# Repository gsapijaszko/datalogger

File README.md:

# yet another datalogger
atmega, sdcard, usb port, DS3231 RTC

work in progress..

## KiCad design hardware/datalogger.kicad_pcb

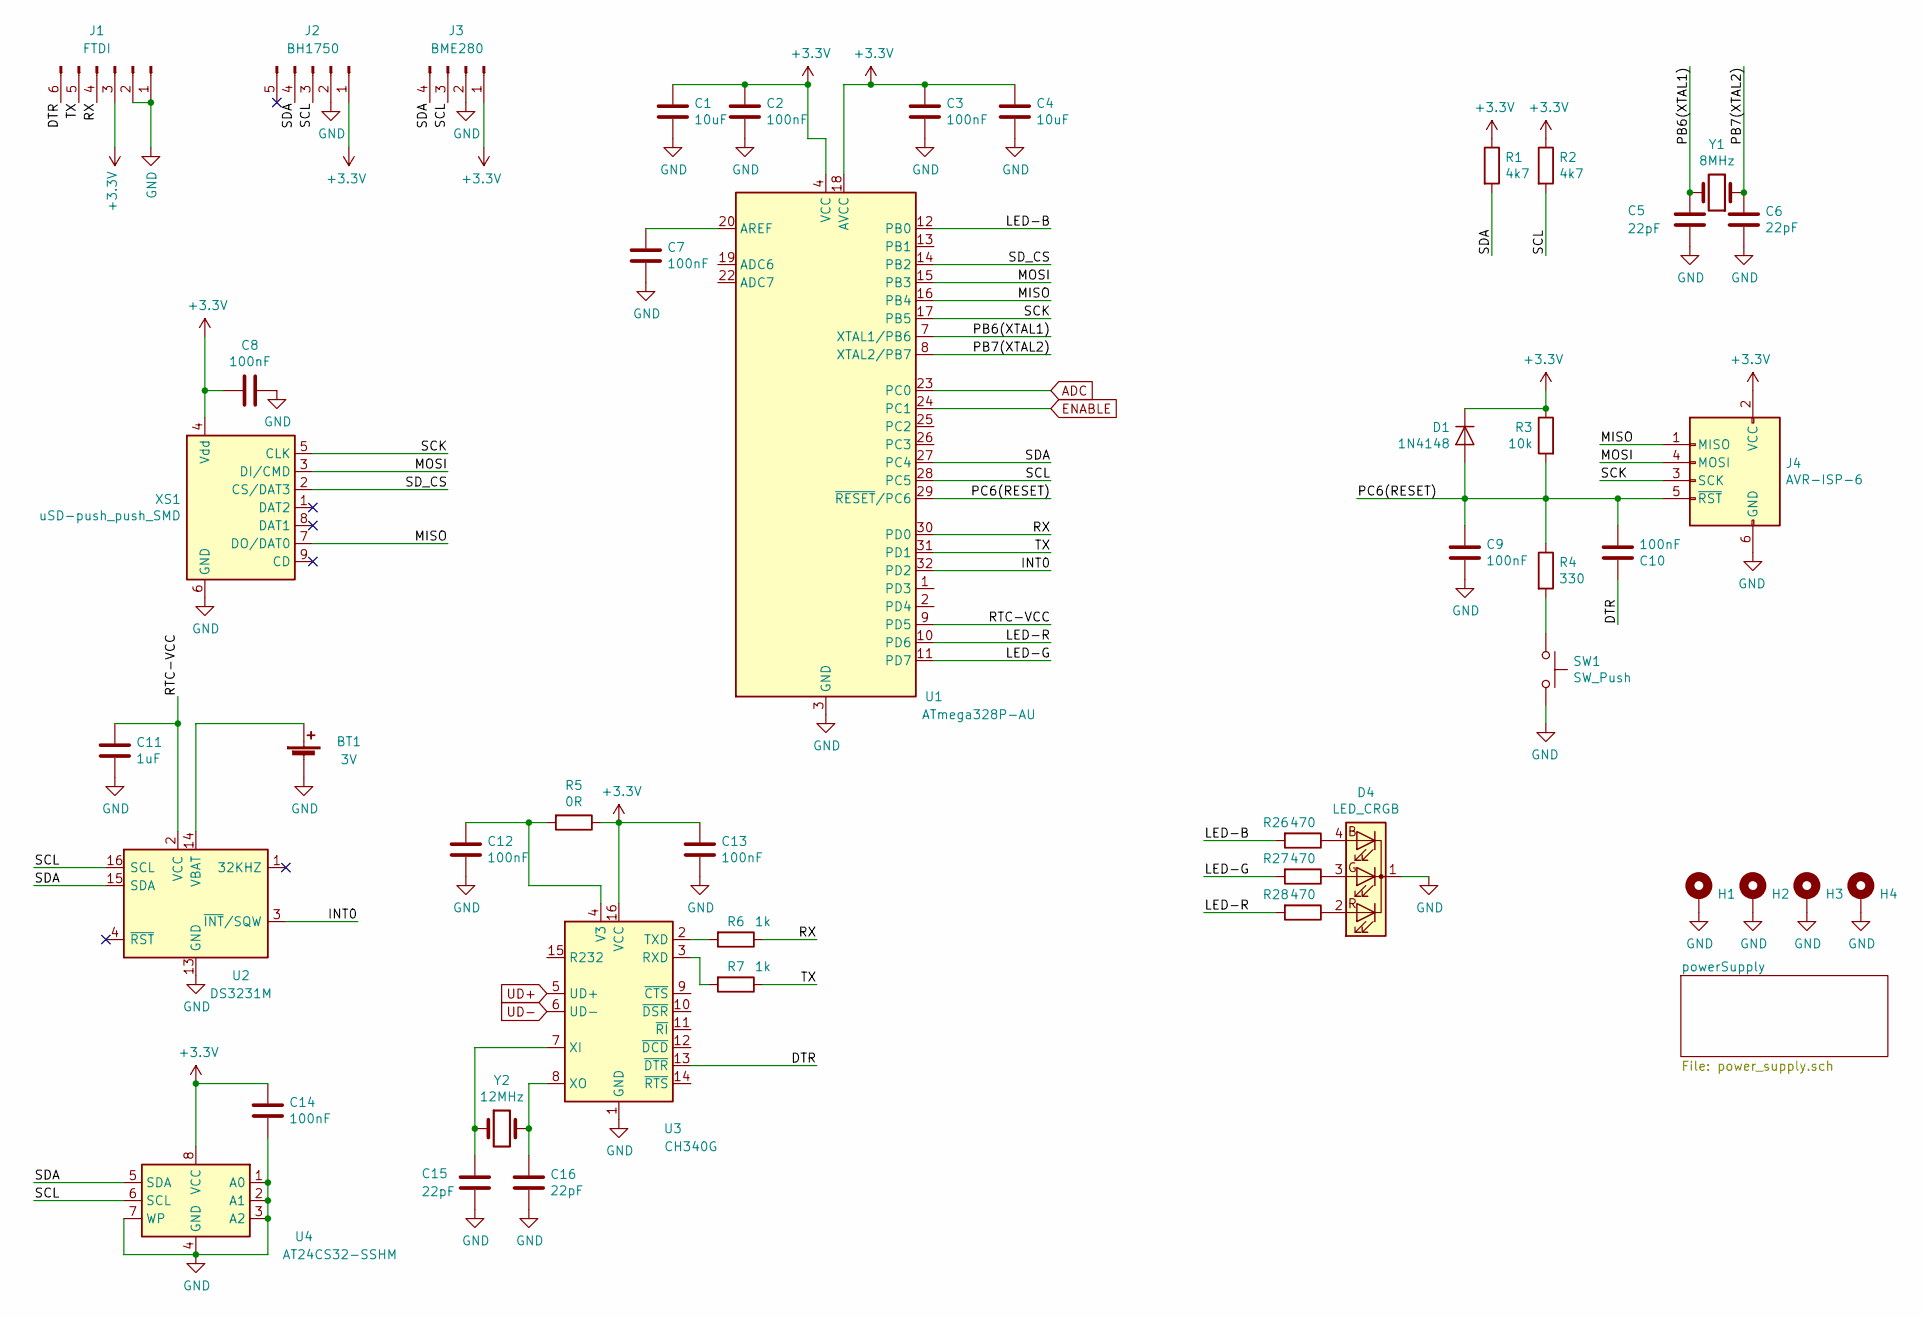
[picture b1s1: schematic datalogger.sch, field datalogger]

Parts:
BT1: 3V; 1220 Battery Holder, SMD
C1, C4: 10uF; C_0805_2012Metric_Pad1.15x1.40mm_HandSolder
C2, C3, C7, C8, C9, C12, C13, C14: 100nF; C_0805_2012Metric_Pad1.15x1.40mm_HandSolder
C5, C6, C15, C16: 22pF; C_1206_3216Metric_Pad1.42x1.75mm_HandSolder
C10: 100nF; C_1206_3216Metric_Pad1.42x1.75mm_HandSolder
C11: 1uF; C_0805_2012Metric_Pad1.15x1.40mm_HandSolder
D1: 1N4148; D_DO-34_SOD68_P7.62mm_Horizontal
D4: LED_CRGB; LED_D5.0mm-4_RCGB
H1, H2, H3, H4: H; MountingHole_2.7mm_M2.5_Pad_Via
J1: FTDI; PinHeader_1x06_P2.54mm_Vertical
J2: BH1750; Molex_KK-254_AE-6410-05A_1x05_P2.54mm_Vertical
J3: BME280; Molex_KK-254_AE-6410-04A_1x04_P2.54mm_Vertical
J4: AVR-ISP-6; IDC-Header_2x03_P2.54mm_Vertical
R1, R2: 4k7; R_0805_2012Metric_Pad1.15x1.40mm_HandSolder
R3: 10k; R_1206_3216Metric_Pad1.42x1.75mm_HandSolder
R4: 330; R_0805_2012Metric_Pad1.15x1.40mm_HandSolder
R5: 0R; R_0805_2012Metric_Pad1.15x1.40mm_HandSolder
R6, R7: 1k; R_0805_2012Metric_Pad1.15x1.40mm_HandSolder
R26, R27, R28: 470; R_1206_3216Metric_Pad1.42x1.75mm_HandSolder
SW1: SW_Push; SW_Tactile_SKHH_Angled
U1: ATmega328P-AU; TQFP-32_7x7mm_P0.8mm
U2: DS3231M; SOIC-16W_7.5x10.3mm_P1.27mm
U3: CH340G; SOIC-16_3.9x9.9mm_P1.27mm
U4: AT24CS32-SSHM; SOIC-8_3.9x4.9mm_P1.27mm
XS1: uSD-push_push_SMD; Conn_uSDcard
Y1: 8MHz; Crystal_HC49-U_Vertical
Y2: 12MHz; Crystal_HC49-U_Vertical

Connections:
+3V3: C1.1, C2.2, C3.2, C4.1, C8.1, C13.2, C14.1, D1.1 (K), J1.3, J2.1, J3.1, J4.2 (VCC), R1.1, R2.1, R3.1, R5.1, U1.4 (VCC), U1.6 (VCC), U1.18 (AVCC), U3.16 (VCC), U4.8 (VCC), XS1.4 (Vdd); also elsewhere on the board
/DTR: C10.1, J1.6, U3.13 (~DTR)
/INT0: U1.32 (PD2), U2.3 (~INT~/SQW)
/LED-B: R26.2, U1.12 (PB0)
/LED-G: R27.2, U1.11 (PD7)
/LED-R: R28.2, U1.10 (PD6)
/MISO: J4.1 (MISO), U1.16 (PB4), XS1.7 (DO/DAT0)
/MOSI: J4.4 (MOSI), U1.15 (PB3), XS1.3 (DI/CMD)
/PB6(XTAL1): C5.1, U1.7 (XTAL1/PB6), Y1.2
/PB7(XTAL2): C6.1, U1.8 (XTAL2/PB7), Y1.1
/PC6(RESET): C9.1, C10.2, D1.2 (A), J4.5 (~RST), R3.2, R4.1, U1.29 (~RESET~/PC6)
/RTC-VCC: C11.1, U1.9 (PD5), U2.2 (VCC)
/RX: J1.4, R6.1, U1.30 (PD0)
/SCK: J4.3 (SCK), U1.17 (PB5), XS1.5 (CLK)
/SCL: J2.3, J3.3, R2.2, U1.28 (PC5), U2.16 (SCL), U4.6 (SCL)
/SDA: J2.4, J3.4, R1.2, U1.27 (PC4), U2.15 (SDA), U4.5 (SDA)
/SD_CS: U1.14 (PB2), XS1.2 (CS/DAT3)
/TX: J1.5, R7.1, U1.31 (PD1)
ADC: U1.23 (PC0); also elsewhere on the board
ENABLE: U1.24 (PC1); also elsewhere on the board
GND: BT1.2 (-), C1.2, C2.1, C3.1, C4.2, C5.2, C6.2, C7.2, C8.2, C9.2, C11.2, C12.1, C13.1, C14.2, C15.2, C16.2, D4.1 (K), H1.1, H2.1, H3.1, H4.1, J1.1, J1.2, J2.2, J3.2, J4.6 (GND), SW1.2, U1.3 (GND), U1.5 (GND), U1.21 (GND), U2.5 (GND), U2.6 (GND), U2.7 (GND), U2.8 (GND), U2.9 (GND), U2.10 (GND), U2.11 (GND), U2.12 (GND), U2.13 (GND), U3.1 (GND), U4.1 (A0), U4.2 (A1), U4.3 (A2), U4.4 (GND), U4.7 (WP), XS1.6 (GND); also elsewhere on the board
unnamed: BT1.1 (+), U2.14 (VBAT)
unnamed: C7.1, U1.20 (AREF)
unnamed: C12.2, R5.2, U3.4 (V3)
unnamed: C15.1, U3.7 (XI), Y2.1
unnamed: C16.1, U3.8 (XO), Y2.2
unnamed: D4.2 (RA), R28.1
unnamed: D4.3 (GA), R27.1
unnamed: D4.4 (BA), R26.1
unnamed: R4.2, SW1.1
unnamed: R6.2, U3.2 (TXD)
unnamed: R7.2, U3.3 (RXD)
UD+: U3.5 (UD+); also elsewhere on the board
UD-: U3.6 (UD-); also elsewhere on the board

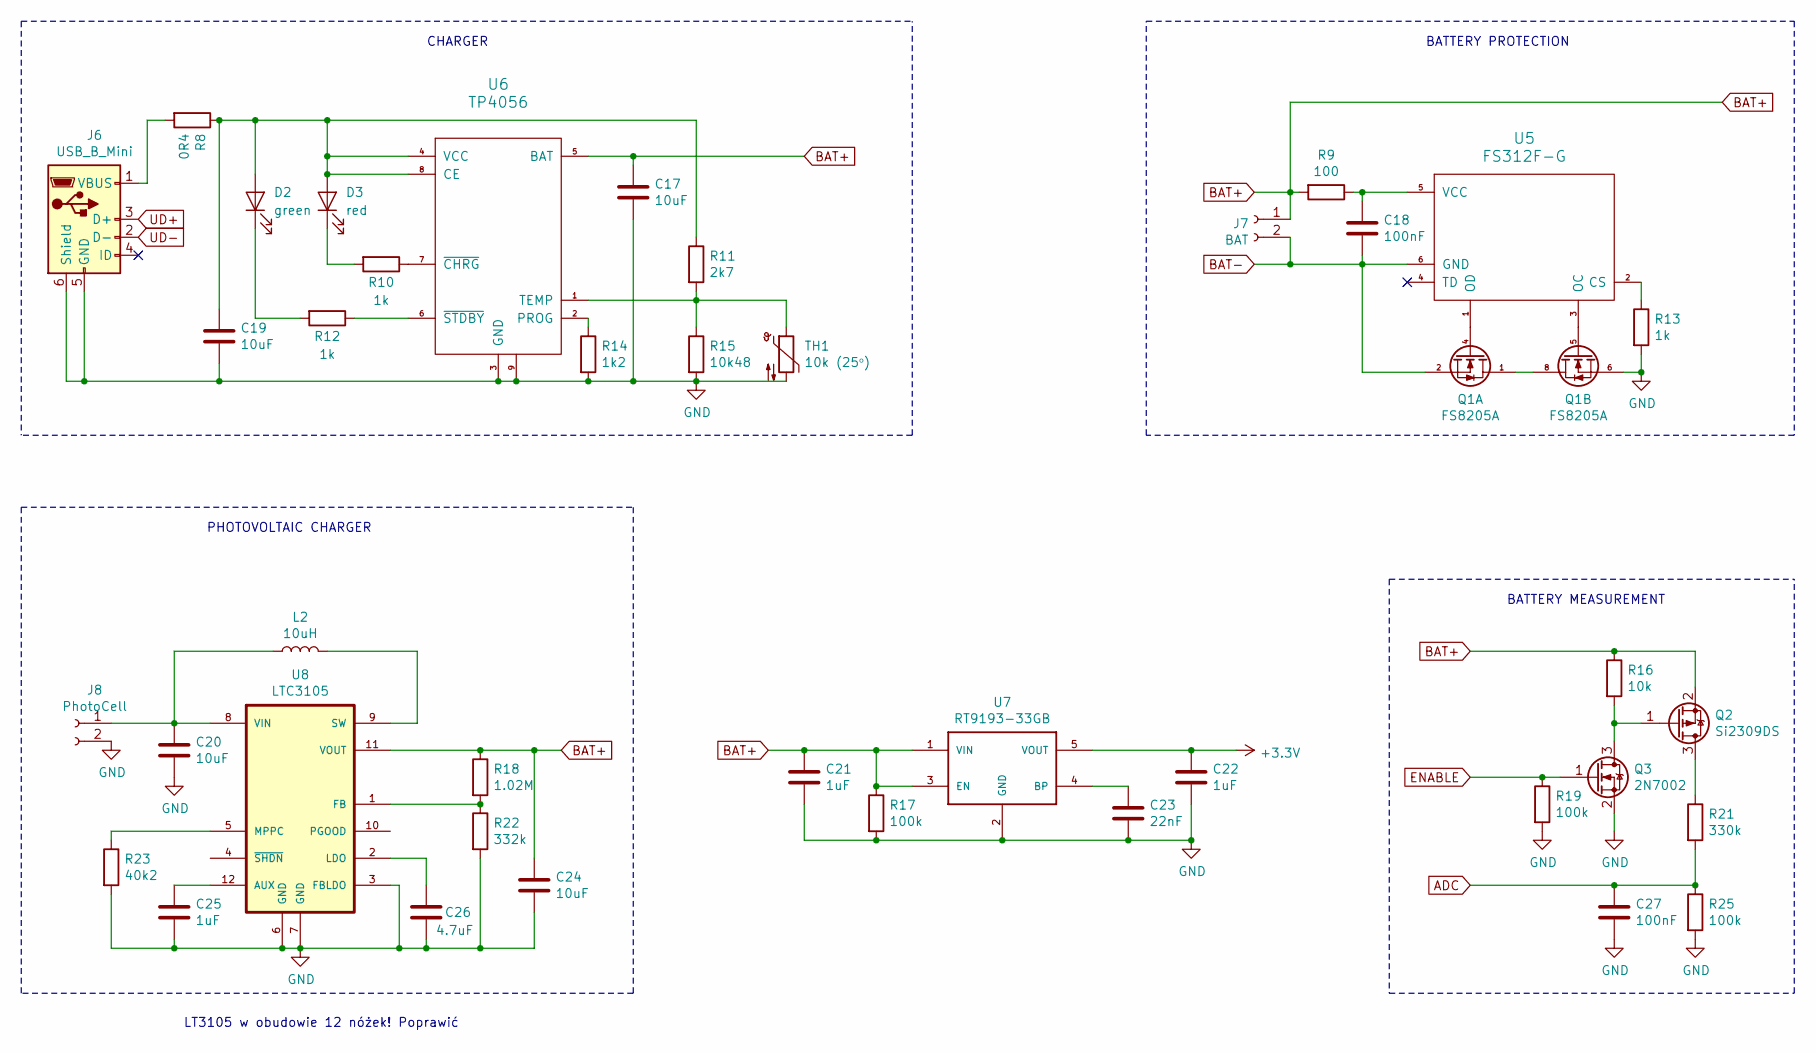
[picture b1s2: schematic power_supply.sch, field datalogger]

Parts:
C17, C19, C20, C24: 10uF; C_1206_3216Metric_Pad1.42x1.75mm_HandSolder
C18, C27: 100nF; C_0805_2012Metric_Pad1.15x1.40mm_HandSolder
C21, C22: 1uF; C_0805_2012Metric_Pad1.15x1.40mm_HandSolder
C23: 22nF; C_0805_2012Metric_Pad1.15x1.40mm_HandSolder
C25: 1uF; C_0805_2012Metric
C26: 4.7uF; C_0805_2012Metric
D2: green; LED_1210_3225Metric_Pad1.42x2.65mm_HandSolder
D3: red; LED_1210_3225Metric_Pad1.42x2.65mm_HandSolder
J6: USB_B_Mini; USB_Micro-B_Wuerth_629105150521
J7: BAT; JST_XH_S02B-XH-A_1x02_P2.50mm_Horizontal
J8: PhotoCell; TerminalBlock_Altech_AK300-2_P5.00mm
L2: 10uH; L_7.3x7.3_H4.5
Q1: FS8205A; TSSOP-8_4.4x3mm_P0.65mm
Q2: Si2309DS; SOT-23
Q3: 2N7002; TSOT-23
R8: 0R4; R_1210_3225Metric_Pad1.42x2.65mm_HandSolder
R9: 100; R_1206_3216Metric_Pad1.42x1.75mm_HandSolder
R10, R12, R13: 1k; R_0805_2012Metric_Pad1.15x1.40mm_HandSolder
R11: 2k7; R_1206_3216Metric_Pad1.42x1.75mm_HandSolder
R14: 1k2; R_1206_3216Metric_Pad1.42x1.75mm_HandSolder
R15: 10k48; R_0805_2012Metric_Pad1.15x1.40mm_HandSolder
R16: 10k; R_1206_3216Metric_Pad1.42x1.75mm_HandSolder
R17, R19, R25: 100k; R_1206_3216Metric_Pad1.42x1.75mm_HandSolder
R18: 1.02M; R_1206_3216Metric_Pad1.42x1.75mm_HandSolder
R21: 330k; R_1206_3216Metric_Pad1.42x1.75mm_HandSolder
R22: 332k; R_1206_3216Metric_Pad1.42x1.75mm_HandSolder
R23: 40k2; R_1206_3216Metric_Pad1.42x1.75mm_HandSolder
TH1: 10k (25ᵒ); R_1218_3246Metric_Pad1.22x4.75mm_HandSolder
U5: FS312F-G; SOT-23-6_Handsoldering
U6: TP4056; HSOP-8-1EP_3.9x4.9mm_P1.27mm_EP2.41x3.1mm_ThermalVias
U7: RT9193-33GB; SOT-23-5_HandSoldering
U8: LTC3105; MSOP-12_3x4mm_P0.65mm

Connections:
+3V3: C22.1, U7.5 (VOUT); also elsewhere on the board
ADC: C27.1, R21.2, R25.1; also elsewhere on the board
BAT+: C17.1, C21.1, C24.1, J7.1, Q2.2 (S), R9.2, R16.1, R17.1, R18.1, U6.5 (BAT), U7.1 (VIN), U7.3 (EN), U8.11 (VOUT)
BAT-: C18.2, J7.2, Q1.2 (S1), U5.6 (GND)
ENABLE: Q3.1 (G), R19.1; also elsewhere on the board
GND: C17.2, C19.2, C20.2, C21.2, C22.2, C23.2, C24.2, C25.2, C26.2, C27.2, J6.5 (GND), J6.6 (Shield), J8.2, Q1.6 (S1), Q3.2 (S), R13.2, R14.2, R15.2, R17.2, R19.2, R22.2, R23.2, R25.2, TH1.2, U6.3 (GND), U6.9, U7.2 (GND), U8.3 (FBLDO), U8.6 (GND), U8.7 (GND); also elsewhere on the board
unnamed: C18.1, R9.1, U5.5 (VCC)
unnamed: C19.1, D2.2 (A), D3.2 (A), R8.1, R11.1, U6.4 (VCC), U6.8 (CE)
unnamed: C20.1, J8.1, L2.1, U8.8 (VIN)
unnamed: C23.1, U7.4 (BP)
unnamed: C25.1, U8.12 (AUX)
unnamed: C26.1, U8.2 (LDO)
unnamed: D2.1 (K), R12.2
unnamed: D3.1 (K), R10.2
unnamed: J6.1 (VBUS), R8.2
unnamed: L2.2, U8.9 (SW)
unnamed: Q1.1 (D), Q1.8 (D)
unnamed: Q1.4 (G2), U5.1 (OD)
unnamed: Q1.5 (G2), U5.3 (OC)
unnamed: Q2.1 (G), Q3.3 (D), R16.2
unnamed: Q2.3 (D), R21.1
unnamed: R10.1, U6.7 (~CHRG)
unnamed: R11.2, R15.1, TH1.1, U6.1 (TEMP)
unnamed: R12.1, U6.6 (~STDBY)
unnamed: R13.1, U5.2 (CS)
unnamed: R14.1, U6.2 (PROG)
unnamed: R18.2, R22.1, U8.1 (FB)
unnamed: R23.1, U8.5 (MPPC)
UD+: J6.3 (D+); also elsewhere on the board
UD-: J6.2 (D-); also elsewhere on the board

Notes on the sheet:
CHARGER
BATTERY PROTECTION
BATTERY MEASUREMENT
PHOTOVOLTAIC CHARGER
LT3105 w obudowie 12 nóżek! Poprawić

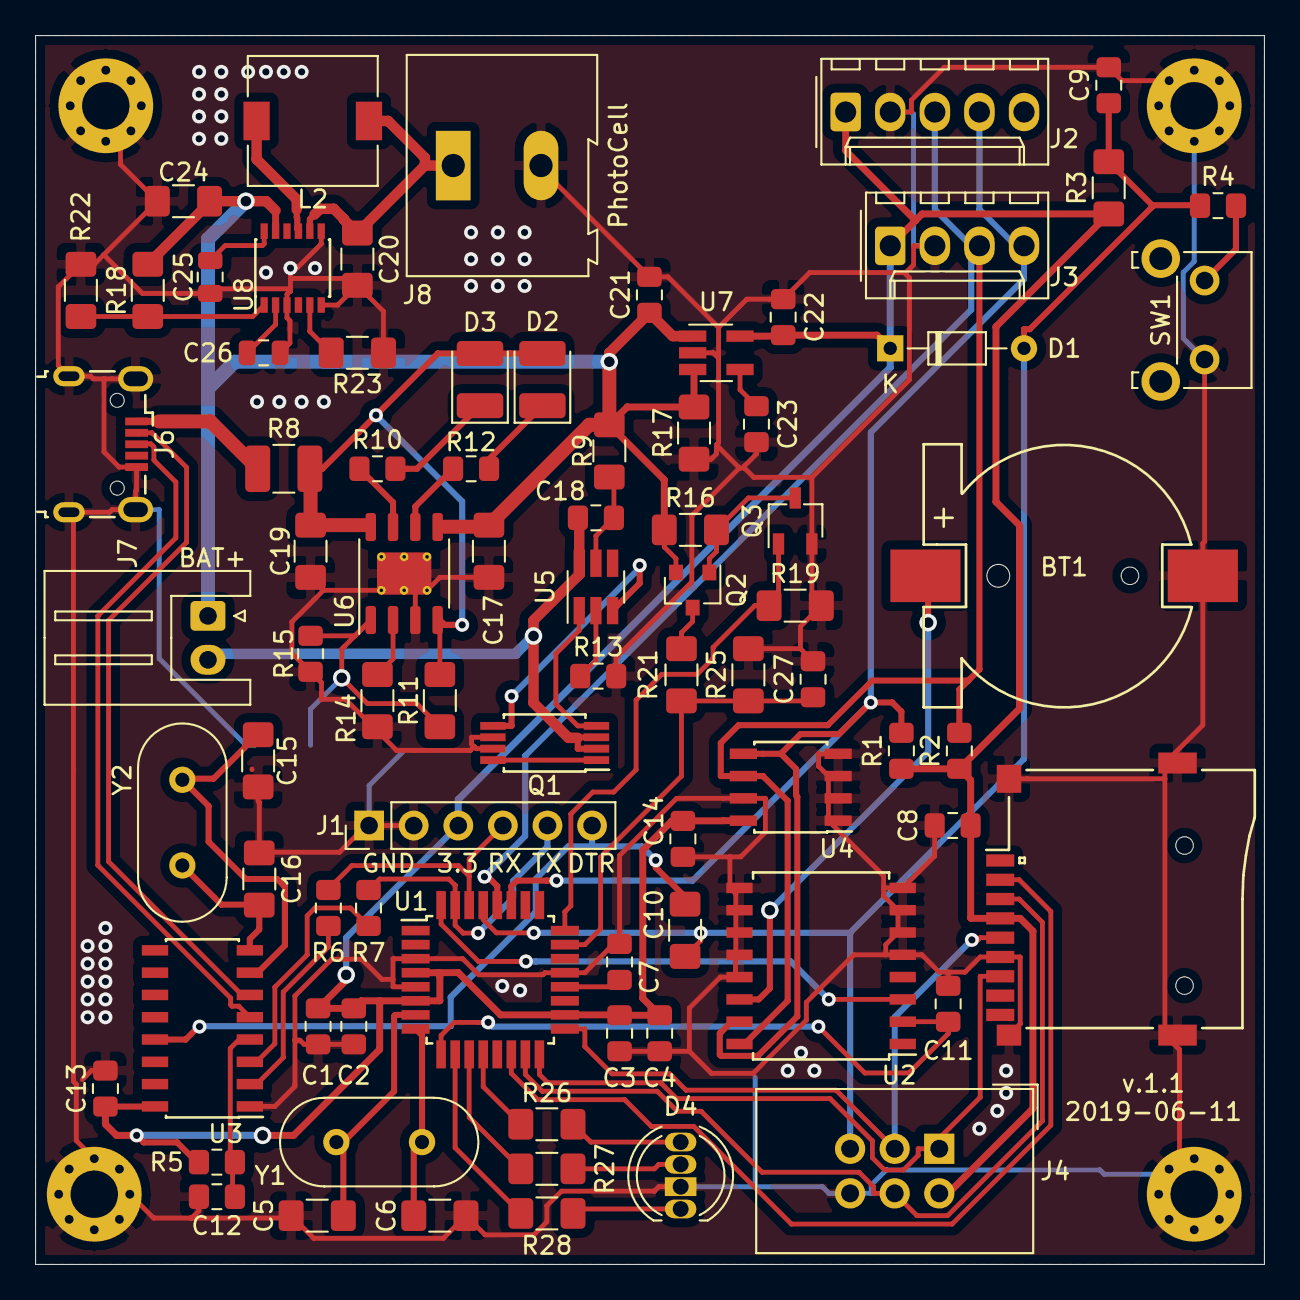
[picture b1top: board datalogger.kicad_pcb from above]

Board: 2 copper layers, 70.0 x 70.0 mm, 86 parts (1 on the bottom side), 58 nets.

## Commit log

2019-04-01 Update LICENSE, README.md, and 31 more files...
2019-04-01 Update datalogger-rescue.dcm, datalogger-rescue.lib, and 3 more files...
2019-04-02 Update fp-info-cache
2019-04-02 Update datalogger-cache.lib, datalogger.bak, and 7 more files...
2019-04-04 Update datalogger.dsn, datalogger.jpg, and 6 more files...
2019-04-05 Update datalogger-cache.lib, datalogger-rescue.dcm, and 8 more files...
2019-04-06 Update _autosave-datalogger.kicad_pcb, datalogger.jpg, and 2 more files...
2019-04-13 Update datalogger-cache.lib, datalogger-rescue.lib, and 11 more files...
2019-04-13 Update datalogger.jpg, datalogger.kicad_pcb, and 2 more files...
2019-04-14 Update datalogger.kicad_pcb and datalogger.kicad_pcb-bak
2019-04-18 Update datalogger.kicad_pcb, datalogger.kicad_pcb-bak, and fp-info-cache
2019-04-26 Update datalogger-cache.lib, datalogger-rescue.bck, and 11 more files...
2019-04-28 Update datalogger-cache.lib, datalogger.bak, and 6 more files...
2019-04-29 Update datalogger-cache.lib, datalogger.kicad_pcb, and 19 more files...
2019-04-29 v.1.0 ready for PCB manufacturing
2019-05-28 Update datalogger_gerbers.zip, fp-info-cache, and 2 more files...
2019-06-06 Update datalogger-cache.lib, datalogger.bak, and 20 more files...
2019-06-11 Change from buck-bost converter to 3.3V LDO
2019-06-12 v. 1.1, sent to PCB
